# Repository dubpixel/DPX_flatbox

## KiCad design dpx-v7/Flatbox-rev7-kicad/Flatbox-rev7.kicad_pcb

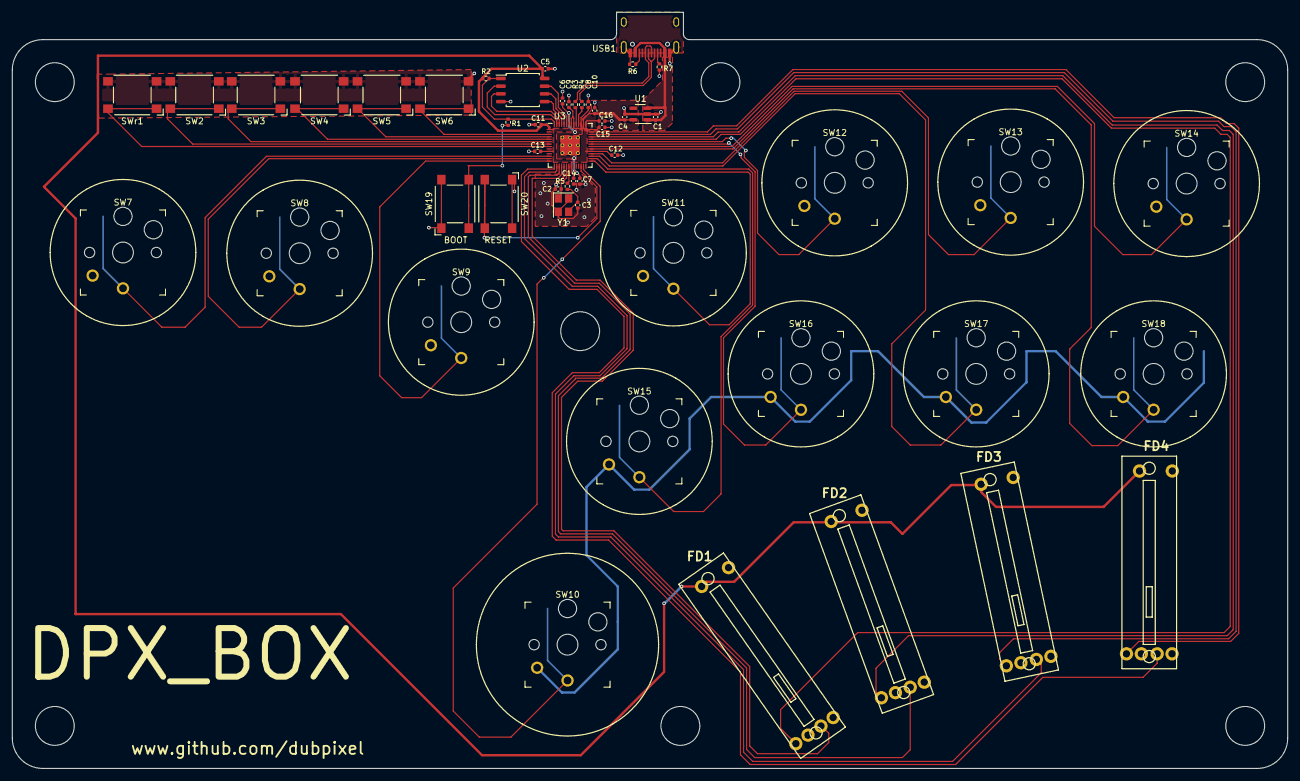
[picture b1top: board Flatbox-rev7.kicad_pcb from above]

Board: 2 copper layers, 210.0 x 124.5 mm, 52 parts (0 on the bottom side), 47 nets.

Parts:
C1, C4, C8, C10: 1u; C_0402_1005Metric
C2, C3: 30p; C_0402_1005Metric
C5, C6, C7, C9, C11, C12, C13, C14, C15, C16: 100n; C_0402_1005Metric
F1, F2, F3, F4: BOURNS-PTL2043_20mm-slide-pot
R1, R5: 1k; R_0402_1005Metric
R2: 10k; R_0402_1005Metric
R3, R4: 27; R_0402_1005Metric
R6, R7: 5.1k; R_0402_1005Metric
SW2, SW3, SW4, SW5, SW6, SW19, SW20: SW_Push; SW_SPST_Omron_B3FS-100xP
SW7, SW8, SW9, SW11, SW12, SW13, SW14, SW15, SW16, SW17, SW18: SW_Push; Kailh_socket_PG1350_optional
SW10: SWX10; Kailh_socket_PG1350_optional
SWr1: SW_Push; SW_SPST_Omron_B3FS-100xP
U1: TLV73333PDBV; SOT-23-5
U2: W25Q128JVS; SOIC-8_5.23x5.23mm_P1.27mm
U3: RP2040; RP2040-QFN-56
USB1: HRO-TYPE-C-31-M-12; HRO-TYPE-C-31-M-12-Assembly
Y1: Crystal_GND24; Crystal_SMD_3225-4Pin_3.2x2.5mm

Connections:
+1V1: C6.1, C7.1, C8.1, U3.23 (DVDD), U3.45 (VREG_VOUT), U3.50 (DVDD)
+3V3: C4.1, C5.1, C9.1, C10.1, C11.1, C12.1, C13.1, C14.1, C15.1, C16.1, F1.3, F2.3, F3.3, F4.3, R2.1, U1.5 (OUT), U2.8 (VCC), U3.1 (IOVDD), U3.10 (IOVDD), U3.22 (IOVDD), U3.33 (IOVDD), U3.42 (IOVDD), U3.43 (ADC_AVDD), U3.44 (VREG_IN), U3.48 (USB_VDD), U3.49 (IOVDD)
+5V: C1.1, U1.1 (IN), U1.3 (EN), USB1.2 (VBUS), USB1.11 (VBUS)
ADC0: F1.2, U3.38 (GPIO26_ADC0)
ADC1: F2.2, U3.39 (GPIO27_ADC1)
ADC2: F3.2, U3.40 (GPIO28_ADC2)
ADC3: F4.2, U3.41 (GPIO29_ADC3)
D+: R3.1, USB1.6 (DP1), USB1.8 (DP2)
D-: R4.1, USB1.5 (DN2), USB1.7 (DN1)
GND: C1.2, C2.1, C3.2, C4.2, C5.2, C6.2, C7.2, C8.2, C9.2, C10.2, C11.2, C12.2, C13.2, C14.2, C15.2, C16.2, F1.1, F1.C (CATHODE), F2.C (CATHODE), F3.1, F3.C (CATHODE), F4.1, F4.C (CATHODE), R6.2, R7.2, SW2.2, SW3.2, SW4.2, SW5.2, SW6.2, SW7.2, SW8.2, SW9.2, SW10.2, SW11.2, SW12.2, SW13.2, SW14.2, SW15.2, SW16.2, SW17.2, SW18.2, SW19.1, SW20.1, SWr1.2, U1.2 (GND), U2.4 (GND), U3.19 (TESTEN), U3.57 (GND), USB1.1 (GND), USB1.12 (GND), USB1.13 (SHIELD), Y1.2, Y1.4
LEDF1: F4.L (EN), U3.15 (GPIO12)
LEDF2: F3.L (EN), U3.16 (GPIO13)
LEDF3: F2.L (EN), U3.17 (GPIO14)
LEDF4: F1.L (EN), U3.18 (GPIO15)
unnamed: C3.1, R5.1, Y1.3
unnamed: R1.2, SW19.2
unnamed: SW20.2, U3.26 (RUN)
unnamed: R4.2, U3.46 (USB_DM)
unnamed: R3.2, U3.47 (USB_DP)
unnamed: R7.1, USB1.4 (CC1)
unnamed: R6.1, USB1.10 (CC2)
QSPI_SCLK: U2.6 (CLK), U3.52 (QSPI_SCLK)
QSPI_SD0: U2.5 (DI(IO0)), U3.53 (QSPI_SD0)
QSPI_SD1: U2.2 (DO(IO1)), U3.55 (QSPI_SD1)
QSPI_SD2: U2.3 (IO2), U3.54 (QSPI_SD2)
QSPI_SD3: U2.7 (IO3), U3.51 (QSPI_SD3)
QSPI_SS: R1.1, R2.2, U2.1 (~CS), U3.56 (QSPI_SS)
SWX1: SWr1.1, U3.8 (GPIO6)
SWX2: SW2.1, U3.7 (GPIO5)
SWX3: SW3.1, U3.6 (GPIO4)
SWX4: SW4.1, U3.5 (GPIO3)
SWX5: SW5.1, U3.4 (GPIO2)
SWX6: SW6.1, U3.3 (GPIO1)
SWX7: SW7.1, U3.12 (GPIO9)
SWX8: SW8.1, U3.13 (GPIO10)
SWX9: SW9.1, U3.14 (GPIO11)
SWX10: SW10.1, U3.27 (GPIO16)
SWX11: SW11.1, U3.29 (GPIO18)
SWX12: SW12.1, U3.37 (GPIO25)
SWX13: SW13.1, U3.32 (GPIO21)
SWX14: SW14.1, U3.35 (GPIO23)
SWX15: SW15.1, U3.30 (GPIO19)
SWX16: SW16.1, U3.36 (GPIO24)
SWX17: SW17.1, U3.31 (GPIO20)
SWX18: SW18.1, U3.34 (GPIO22)
XIN: C2.2, U3.20 (XIN), Y1.1
XOUT: R5.2, U3.21 (XOUT)

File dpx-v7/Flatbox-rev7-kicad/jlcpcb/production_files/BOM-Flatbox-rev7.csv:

Comment,Designator,Footprint,LCSC
1k,"R1,R5",R_0402_1005Metric,C11702
TLV73333PDBV,U1,SOT-23-5,C134139
27,"R3,R4",R_0402_1005Metric,C138021
100n,"C11,C12,C13,C14,C15,C16,C5,C6,C7,C9",C_0402_1005Metric,C1525
30p,"C2,C3",C_0402_1005Metric,C1570
HRO-TYPE-C-31-M-12,USB1,HRO-TYPE-C-31-M-12-Assembly,C165948
RP2040,U3,RP2040-QFN-56,C2040
10k,R2,R_0402_1005Metric,C25744
5.1k,"R6,R7",R_0402_1005Metric,C25905
SW_Push,"SW19,SW2,SW20,SW3,SW4,SW5,SW6,SWr1",SW_SPST_Omron_B3FS-100xP,C271750
SWX10,"SW10,SW11,SW12,SW13,SW14,SW15,SW16,SW17,SW18,SW7,SW8,SW9",Kailh_socket_PG1350_optional,C400231
1u,"C1,C10,C4,C8",C_0402_1005Metric,C52923
Crystal_GND24,Y1,Crystal_SMD_3225-4Pin_3.2x2.5mm,C9002
W25Q128JVS,U2,SOIC-8_5.23x5.23mm_P1.27mm,C97521
~,F2,BOURNS-PTL2043_20mm-slide-pot,
~,F4,BOURNS-PTL2043_20mm-slide-pot,
~,F1,BOURNS-PTL2043_20mm-slide-pot,
~,F3,BOURNS-PTL2043_20mm-slide-pot,

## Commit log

2024-12-09 very messy commit - need to reorg
    very very messy messy. - also includes an RGB fork from @mxd1365
2024-12-09 version-name-change
2024-12-09 manual merge to be in line with main branch
